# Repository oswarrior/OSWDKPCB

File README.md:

OSWDKPCB
========

OSWarrior DK Design Files for Eagle 6.3+

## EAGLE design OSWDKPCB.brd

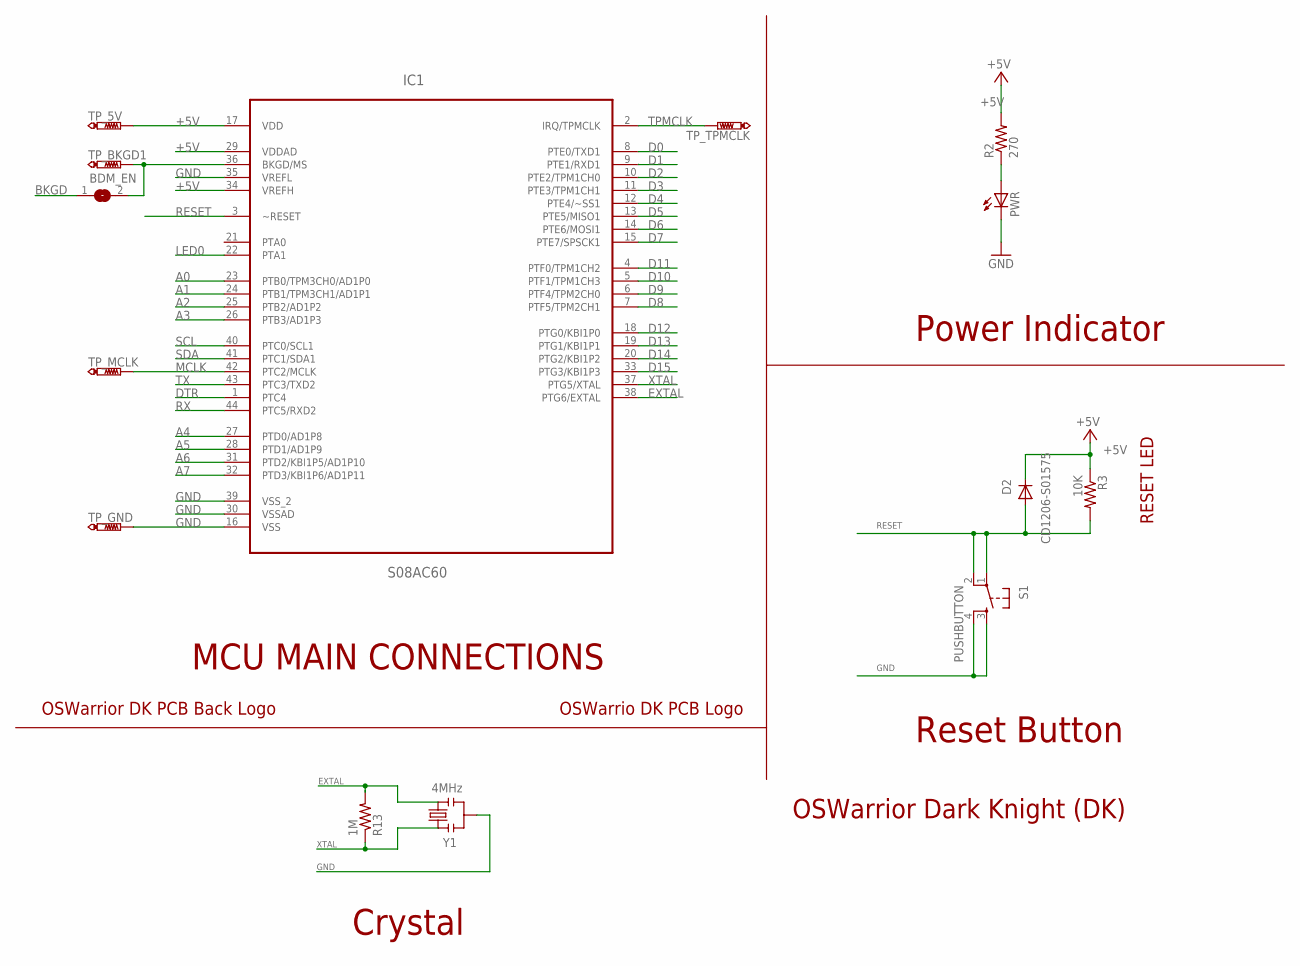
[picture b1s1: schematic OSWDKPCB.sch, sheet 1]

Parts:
BDM_EN: SJ
D2: CD1206-S01575; SOD123
IC1: S08AC60; LQFP-44
PWR: LEDCHIPLED_0805; CHIPLED_0805
R2: 270; M0805
R3: 10K; M0805
R13: 1M; M0805
S1: PUSHBUTTON; TACTILE-PTH
TP_5V: PTR1B1,27; B1,27
TP_BKGD1: PTR1B1,27; B1,27
TP_GND: PTR1B1,27; B1,27
TP_MCLK: PTR1B1,27; B1,27
TP_TPMCLK: PTR1B1,27; B1,27
U$1: OSWDK_LOGO
U$2: OSWDK_BACK_LOGO
Y1: 4MHz; RESONATOR-SMD

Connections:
+5V: D2.C, IC1.17 (VDD), IC1.29 (VDDAD), IC1.34 (VREFH), R2.2, R3.1, TP_5V.TP; also elsewhere on the board
A0: IC1.23 (PTB0/TPM3CH0/AD1P0); also elsewhere on the board
A1: IC1.24 (PTB1/TPM3CH1/AD1P1); also elsewhere on the board
A2: IC1.25 (PTB2/AD1P2); also elsewhere on the board
A3: IC1.26 (PTB3/AD1P3); also elsewhere on the board
A4: IC1.27 (PTD0/AD1P8); also elsewhere on the board
A5: IC1.28 (PTD1/AD1P9); also elsewhere on the board
A6: IC1.31 (PTD2/KBI1P5/AD1P10); also elsewhere on the board
A7: IC1.32 (PTD3/KBI1P6/AD1P11); also elsewhere on the board
BKGD: BDM_EN.1; also elsewhere on the board
D0: IC1.8 (PTE0/TXD1); also elsewhere on the board
D1: IC1.9 (PTE1/RXD1); also elsewhere on the board
D2: IC1.10 (PTE2/TPM1CH0); also elsewhere on the board
D3: IC1.11 (PTE3/TPM1CH1); also elsewhere on the board
D4: IC1.12 (PTE4/~SS1); also elsewhere on the board
D5: IC1.13 (PTE5/MISO1); also elsewhere on the board
D6: IC1.14 (PTE6/MOSI1); also elsewhere on the board
D7: IC1.15 (PTE7/SPSCK1); also elsewhere on the board
D8: IC1.7 (PTF5/TPM2CH1); also elsewhere on the board
D9: IC1.6 (PTF4/TPM2CH0); also elsewhere on the board
D10: IC1.5 (PTF1/TPM1CH3); also elsewhere on the board
D11: IC1.4 (PTF0/TPM1CH2); also elsewhere on the board
D12: IC1.18 (PTG0/KBI1P0); also elsewhere on the board
D13: IC1.19 (PTG1/KBI1P1); also elsewhere on the board
D14: IC1.20 (PTG2/KBI1P2); also elsewhere on the board
D15: IC1.33 (PTG3/KBI1P3); also elsewhere on the board
DTR: IC1.1 (PTC4)
EXTAL: IC1.38 (PTG6/EXTAL), R13.2, Y1.3
GND: IC1.16 (VSS), IC1.30 (VSSAD), IC1.35 (VREFL), IC1.39 (VSS_2), PWR.C, S1.3, S1.4, TP_GND.TP, Y1.2; also elsewhere on the board
LED0: IC1.22 (PTA1); also elsewhere on the board
MCLK: IC1.42 (PTC2/MCLK), TP_MCLK.TP
unnamed: BDM_EN.2, IC1.36 (BKGD/MS), TP_BKGD1.TP
unnamed: PWR.A, R2.1
RESET: D2.A, IC1.3 (~RESET), R3.2, S1.1, S1.2; also elsewhere on the board
RX: IC1.44 (PTC5/RXD2); also elsewhere on the board
SCL: IC1.40 (PTC0/SCL1); also elsewhere on the board
SDA: IC1.41 (PTC1/SDA1); also elsewhere on the board
TPMCLK: IC1.2 (IRQ/TPMCLK), TP_TPMCLK.TP
TX: IC1.43 (PTC3/TXD2); also elsewhere on the board
XTAL: IC1.37 (PTG5/XTAL), R13.1, Y1.1

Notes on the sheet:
MCU MAIN CONNECTIONS
RESET LED
Reset Button
Power Indicator
Crystal

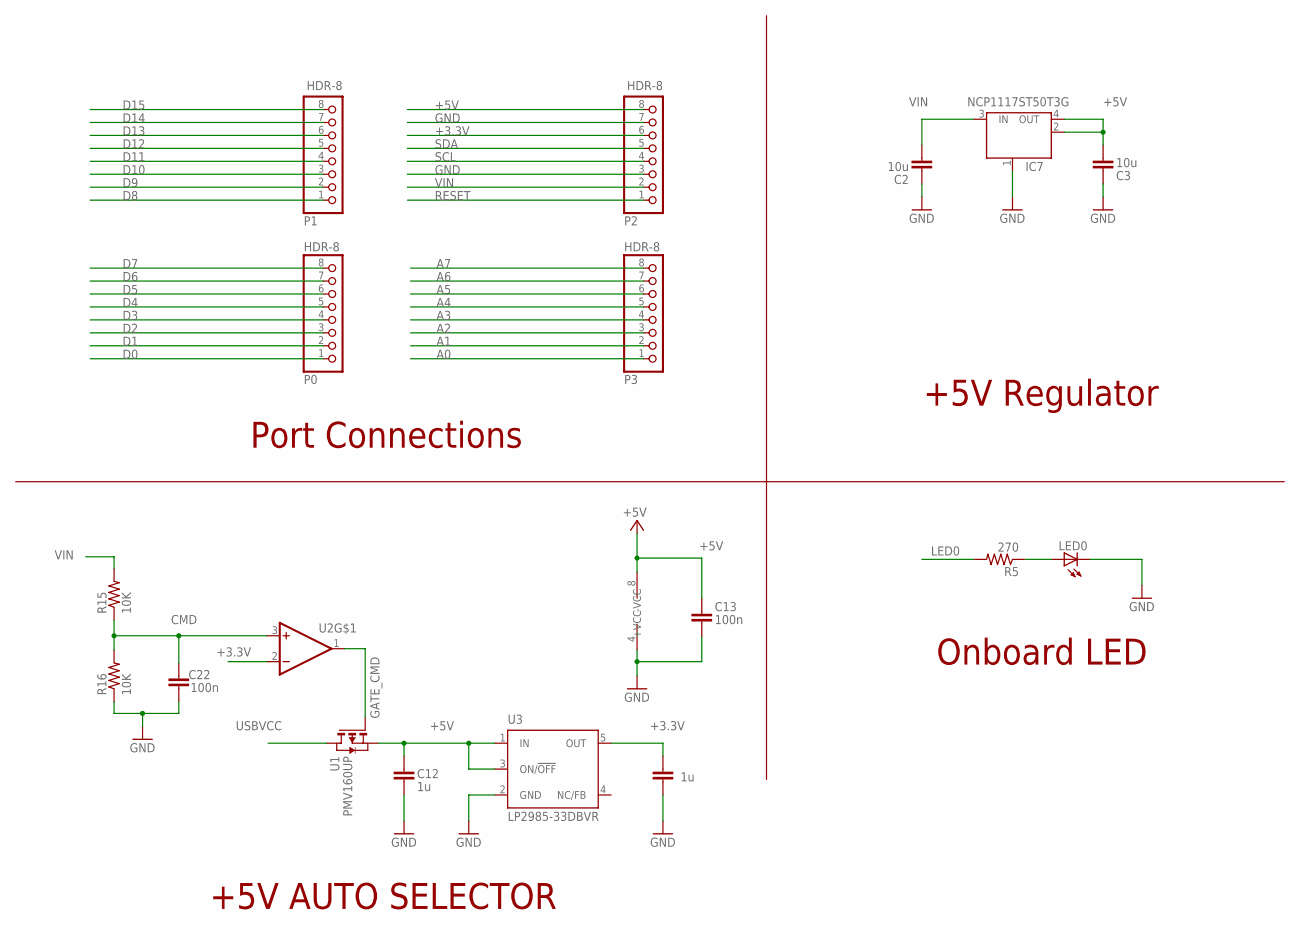
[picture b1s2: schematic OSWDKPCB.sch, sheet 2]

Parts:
C2, C3: 10u; C0805
C12, C14: 1u; C0805
C13, C22: 100n; C0805
IC7: NCP1117ST50T3G; SOT223
LED0: LEDCHIPLED_0805; CHIPLED_0805
P0, P1, P2, P3: HDR-8; 1X08
R5: 270; M0805
R15, R16: 10K; M0805
U1: PMV160UP; SOT-23
U2: RC4558; SOIC-8
U3: LP2985-33DBVR; SOT23-DBV

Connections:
+3.3V: C14.2, P2.6, U2.2 (-IN1), U3.5 (OUT)
+5V: C3.1, C12.2, C13.1, IC7.2 (OUT), IC7.4 (OUT), P2.8, U1.2 (S), U2.8 (+VCC), U3.1 (IN), U3.3 (ON/!OFF); also elsewhere on the board
A0: P3.1; also elsewhere on the board
A1: P3.2; also elsewhere on the board
A2: P3.3; also elsewhere on the board
A3: P3.4; also elsewhere on the board
A4: P3.5; also elsewhere on the board
A5: P3.6; also elsewhere on the board
A6: P3.7; also elsewhere on the board
A7: P3.8; also elsewhere on the board
CMD: C22.2, R15.1, R16.2, U2.3 (+IN1)
D0: P0.1; also elsewhere on the board
D1: P0.2; also elsewhere on the board
D2: P0.3; also elsewhere on the board
D3: P0.4; also elsewhere on the board
D4: P0.5; also elsewhere on the board
D5: P0.6; also elsewhere on the board
D6: P0.7; also elsewhere on the board
D7: P0.8; also elsewhere on the board
D8: P1.1; also elsewhere on the board
D9: P1.2; also elsewhere on the board
D10: P1.3; also elsewhere on the board
D11: P1.4; also elsewhere on the board
D12: P1.5; also elsewhere on the board
D13: P1.6; also elsewhere on the board
D14: P1.7; also elsewhere on the board
D15: P1.8; also elsewhere on the board
GATE_CMD: U1.3 (G), U2.1 (OUT1)
GND: C2.2, C3.2, C12.1, C13.2, C14.1, C22.1, IC7.1 (GND/ADJ), LED0.C, P2.3, P2.7, R16.1, U2.4 (-VCC), U3.2 (GND); also elsewhere on the board
LED0: R5.2; also elsewhere on the board
unnamed: LED0.A, R5.1
RESET: P2.1; also elsewhere on the board
SCL: P2.4; also elsewhere on the board
SDA: P2.5; also elsewhere on the board
USBVCC: U1.1 (D); also elsewhere on the board
VIN: C2.1, IC7.3 (IN), P2.2, R15.2

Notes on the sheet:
Port Connections
Onboard LED
+5V AUTO SELECTOR
+5V Regulator

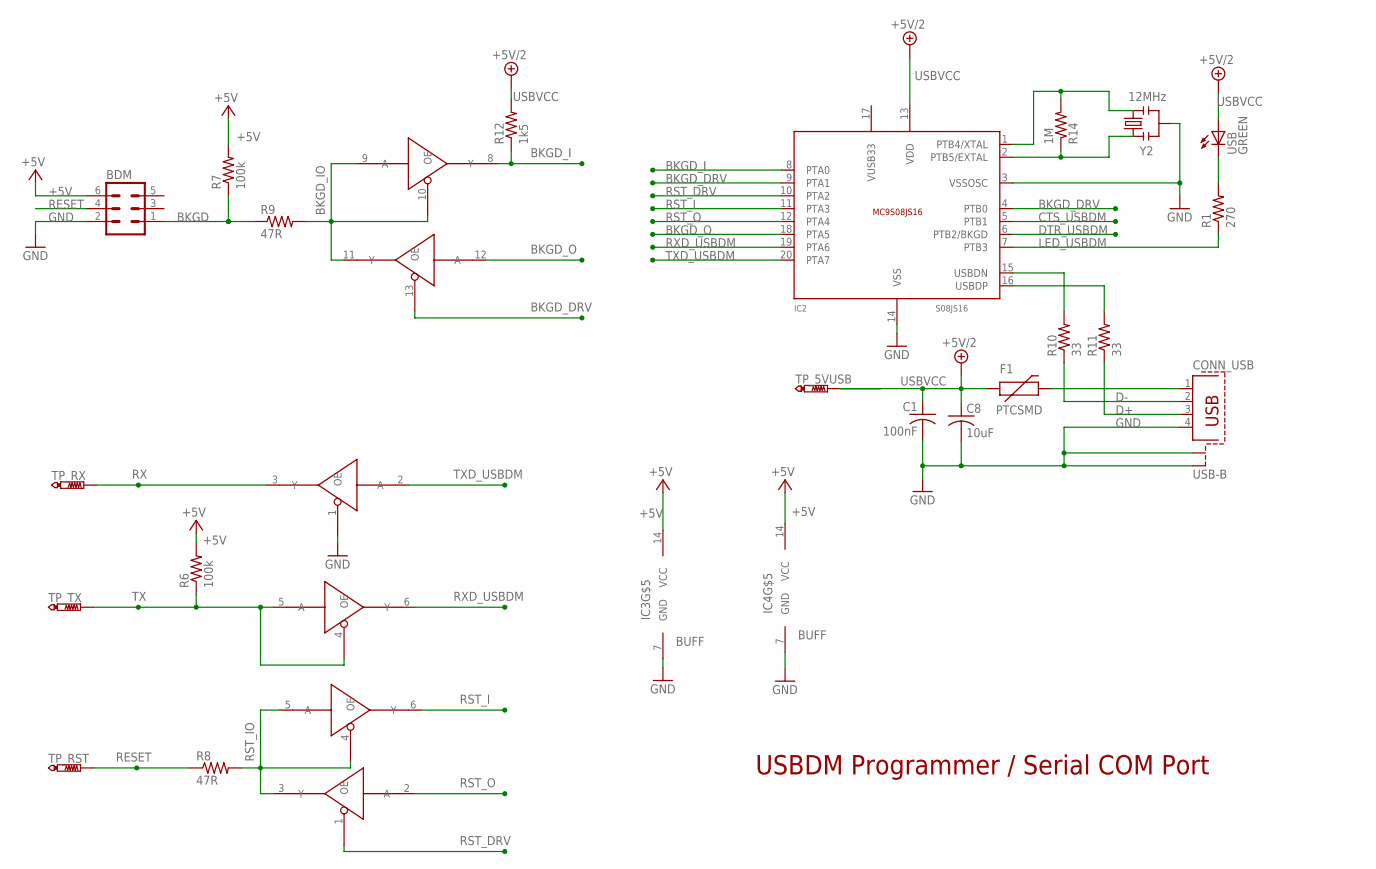
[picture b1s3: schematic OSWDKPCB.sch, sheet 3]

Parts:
BDM: MA03-2
C1: 100nF; C0805
C8: 10uF; C0805
CONN_USB: USB-B; PN61729-S
F1: PTCSMD; PTC-1206
IC2: S08JS16; SOIC-20
IC3, IC4: BUFF; TSSOP-14
R1: 270; M0805
R6, R7: 100k; M0805
R8, R9: 47R; M0805
R10, R11: 33; M0805
R12: 1k5; M0805
R14: 1M; M0805
TP_5VUSB: PTR1B1,27; B1,27
TP_RST: PTR1B1,27; B1,27
TP_RX: PTR1B1,27; B1,27
TP_TX: PTR1B1,27; B1,27
USB: GREEN; CHIPLED_0805
Y2: 12MHz; RESONATOR-SMD

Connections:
+5V: BDM.6, IC3.14 (VCC), IC4.14 (VCC), R6.2, R7.2; also elsewhere on the board
BKGD: BDM.1, R7.1, R9.1; also elsewhere on the board
BKGD_DRV: IC2.4 (PTB0), IC2.9 (PTA1), IC4.13 (OE)
BKGD_I: IC2.8 (PTA0), IC4.8 (Y), R12.1
BKGD_IO: IC4.9 (A), IC4.10 (OE), IC4.11 (Y), R9.2
BKGD_O: IC2.18 (PTA5), IC4.12 (A)
CTS_USBDM: IC2.5 (PTB1)
D+: CONN_USB.3, R11.1
D-: CONN_USB.2, R10.1
DTR_USBDM: IC2.6 (PTB2/BKGD)
GND: BDM.2, C1.2, C8.2, CONN_USB.4, CONN_USB.S1, CONN_USB.S2, IC2.3 (VSSOSC), IC2.14 (VSS), IC3.1 (OE), IC3.7 (GND), IC4.7 (GND), Y2.2; also elsewhere on the board
LED_USBDM: IC2.7 (PTB3), R1.1
unnamed: R1.2, USB.C
unnamed: IC2.15 (USBDN), R10.2
unnamed: IC2.16 (USBDP), R11.2
unnamed: IC2.1 (PTB4/XTAL), R14.2, Y2.3
unnamed: CONN_USB.1, F1.2
unnamed: IC2.2 (PTB5/EXTAL), R14.1, Y2.1
RESET: BDM.4, R8.1, TP_RST.TP; also elsewhere on the board
RST_DRV: IC2.10 (PTA2), IC4.1 (OE)
RST_I: IC2.11 (PTA3), IC4.6 (Y)
RST_IO: IC4.3 (Y), IC4.4 (OE), IC4.5 (A), R8.2
RST_O: IC2.12 (PTA4), IC4.2 (A)
RX: IC3.3 (Y), TP_RX.TP; also elsewhere on the board
RXD_USBDM: IC2.19 (PTA6), IC3.6 (Y)
TX: IC3.4 (OE), IC3.5 (A), R6.1, TP_TX.TP; also elsewhere on the board
TXD_USBDM: IC2.20 (PTA7), IC3.2 (A)
USBVCC: C1.1, C8.1, F1.1, IC2.13 (VDD), R12.2, TP_5VUSB.TP, USB.A; also elsewhere on the board
VUSB33: IC2.17 (VUSB33)

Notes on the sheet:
USBDM Programmer / Serial COM Port

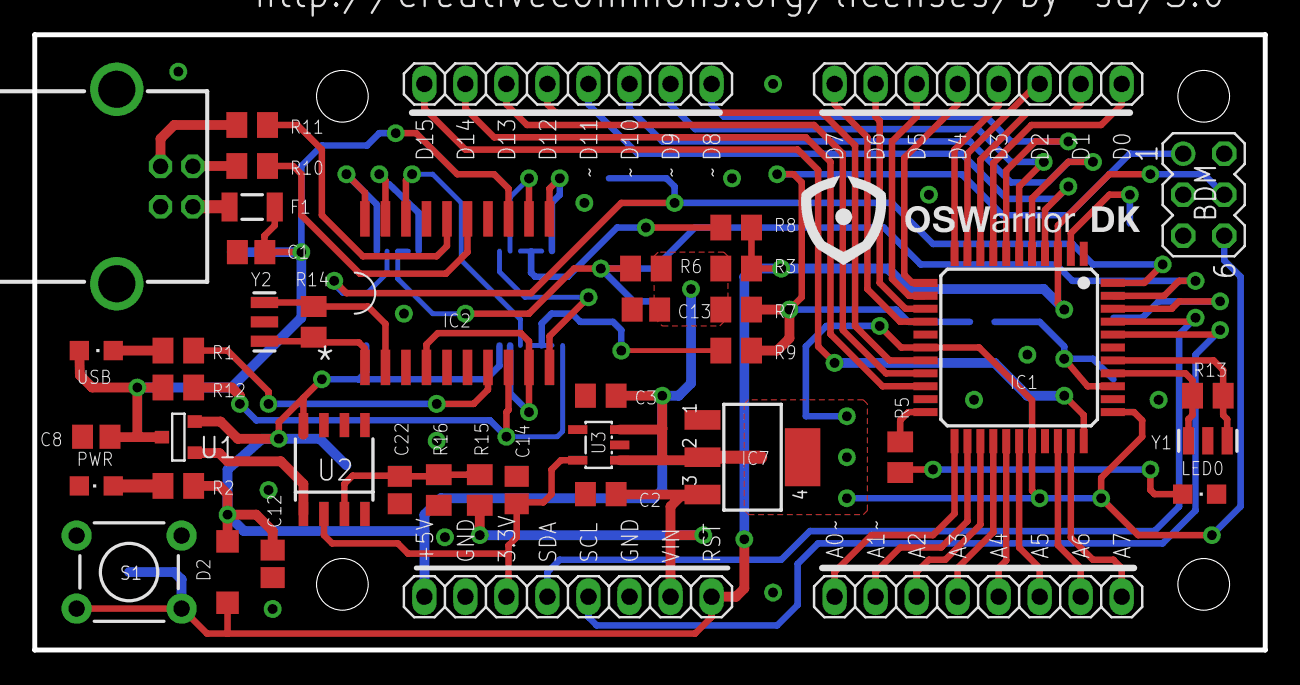
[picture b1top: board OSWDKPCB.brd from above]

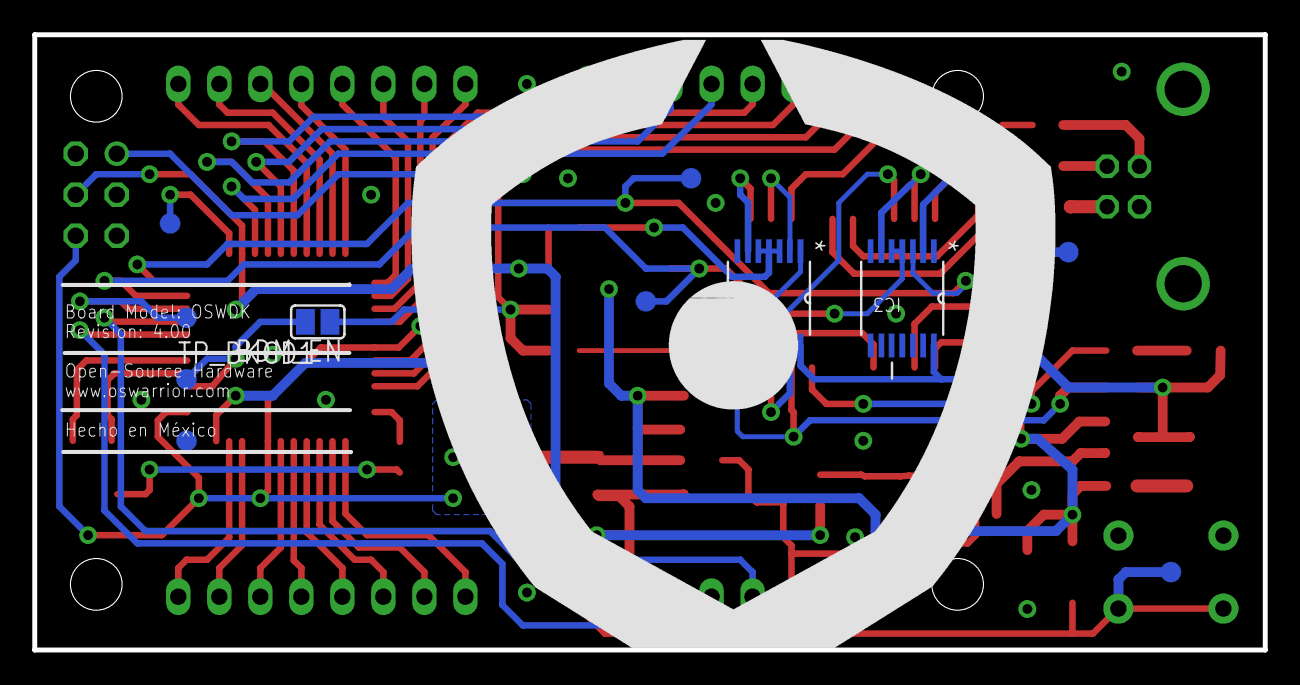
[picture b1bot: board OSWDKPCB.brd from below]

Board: 2 copper layers, 76.2 x 38.1 mm, 57 parts (12 on the bottom side), 64 nets.

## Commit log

2014-02-06 Design files initial Commit
2014-02-06 .brd file updated
2014-02-07 VCC de los buffer
    La alimentación de ambos buffers se ha cambiado a 5V de la tarjeta.
    El logo de la parte trasera se ha actualizado a un simbolo.
    La revision ha cambiado a 4.00
2014-02-27 Silkscreen update.
    This was the last update before the manufcaturing process, this update
    only imprive the logo mark on the PCB, it doesnt have any layout
    changes.
2014-04-16 Version 4.2
    Revision 3.0

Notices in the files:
OSWDKPCB.brd:
Released under the Creative Commons Attribution Share-Alike 3.0 License
http://creativecommons.org/licenses/by-sa/3.0
parts and their libraries:
SparkFun: Licensing: CC v3.0 Share-Alike You are welcome to use this library for commercial purposes.
